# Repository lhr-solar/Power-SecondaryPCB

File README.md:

# Power-SecondaryPCB 
Author: Pratyush Patra and Jason Kacines

This board takes inputs from the DCDC converter and the Supplemental Battery and selects which source to output to the fuse box. DCDC is the power from the high voltage primary battery pack that gets stepped down to 12V through the DCDC converter. The supplemental battery pack is the low voltage 12V NiMH battery pack. When DCDC is on, the board will select DCDC, and when DCDC is off, the board will select the Supplemental Battery. The supplemental should only be selected during ignition and the fault state. The board selects the source using a 10V zener diode that will breakdown once DCDC is above 10V.

This board also interfaces with both the Supplemental Monitoring PCB and Ignition Switch:
- For the Supplemental Monitoring PCB, this board sends the voltage of the Supplemental Battery out from J1. 
- For the Ignition Switch, this board sends Supplemental Power to the Controls Board through J6, which is then routed back to this board through J7 when the Ignition Switch is changed from the off position. When this signal is sent to J7, it is routed to the gate of Q3 which turns on the NMOS and starts sending power to the fuse box.

## BOM
[**Interactive BOM (Must download and open in browser)**](bom/ibom.html)

[**Mouser Cart**](https://www.mouser.com/ProjectManager/ProjectDetail.aspx?AccessID=da938bf7b6)

## Connectors
| # | Name | Type | Ideal Voltage | Notes |
| - | - | - | - | - |
| J1  | SUPP PWR MON | 1x02_P3.00mm_Vertical Female | +12V | 9.9 mm tall |
| J2  | SUPP PWR 1 | 1x02_P7.49mm_Vertical Female |+12V | 14.76 mm tall |
| J3  | SUPP PWR 2 | 1x02_P7.49mm_Vertical Female | +12V | 14.76 mm tall |
| J4  | DCDC PWR | 1x02_P7.49mm_Vertical Female | +12V | 14.76 mm tall |
| J5  | FUSE OUT | 1x02_P7.49mm_Vertical Female | +12V | 14.76 mm tall |
| J6  | SUPP OUT | 1x02_P3.00mm_Vertical Female | +12V | 9.9 mm tall |
| J7  | LV ENABLE | 1x02_P3.00mm_Vertical Female | +12V | 9.9 mm tall |

## PCB

## Schematic

## Additional Notes
The tallest components are the Power MOSFETs(Q1A1, Q1A2, Q1A3, Q1A4) which are 18.5 mm tall and the connectors which are 14.76 mm tall.

## Current Board Concerns(8.26.2023)
- If the two Supplemental Batteries are at different voltage, don't want to charge batteries.
- If the two Supplemental Batteries are above 12V and DCDC is off, don't want to overvolt LV systems. 
        Can tolerate 12.8V.
- Should we use heat sinks for the MOSFET or switch to SMD in case we need to increase current draw in the future
- In future switch to this mosfet, https://www.mouser.com/datasheet/2/196/Infineon_IRFR5305_DataSheet_v01_01_EN-3166466.pdf

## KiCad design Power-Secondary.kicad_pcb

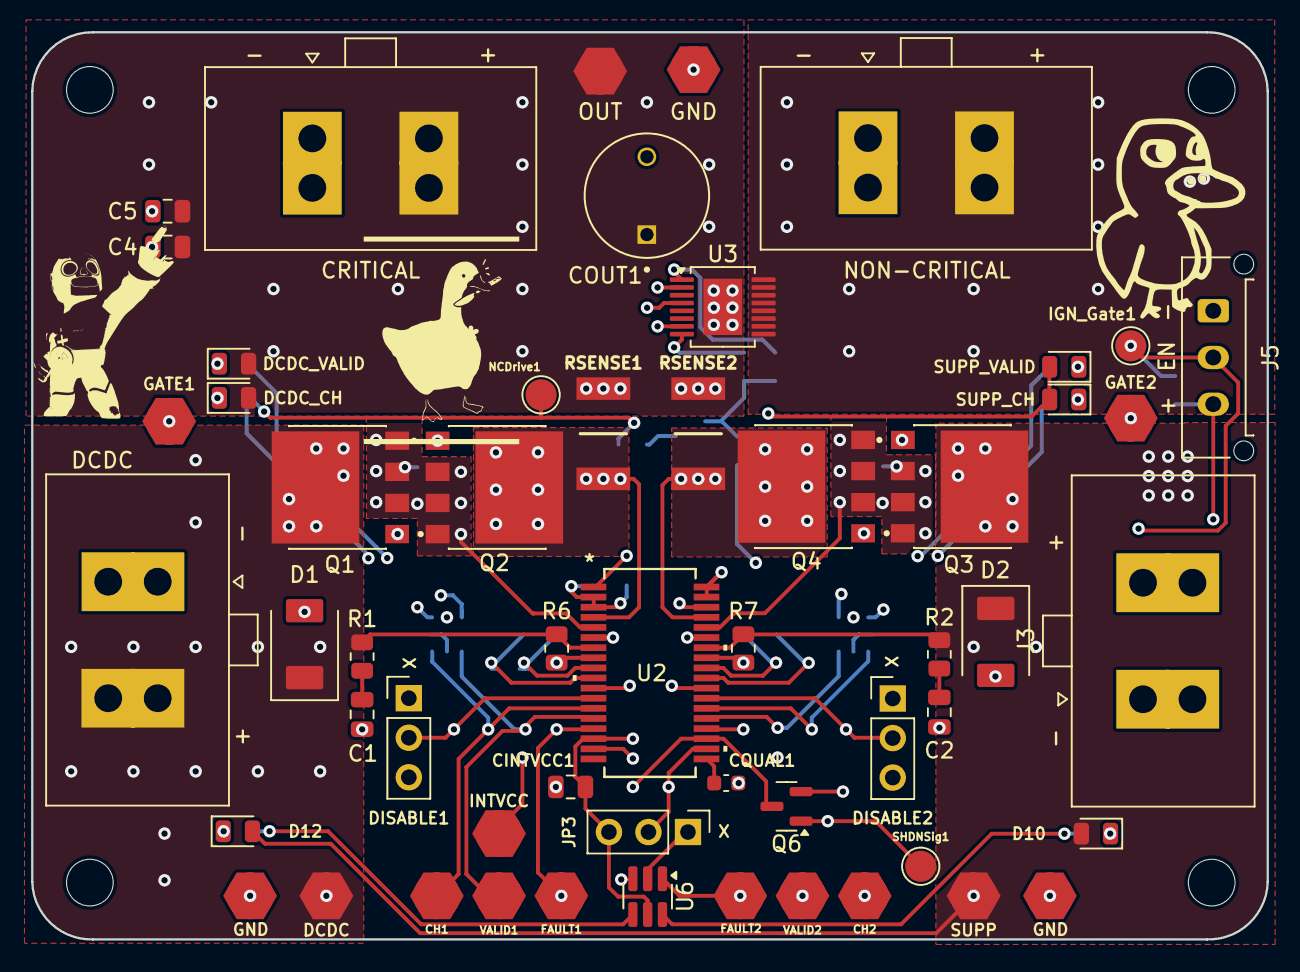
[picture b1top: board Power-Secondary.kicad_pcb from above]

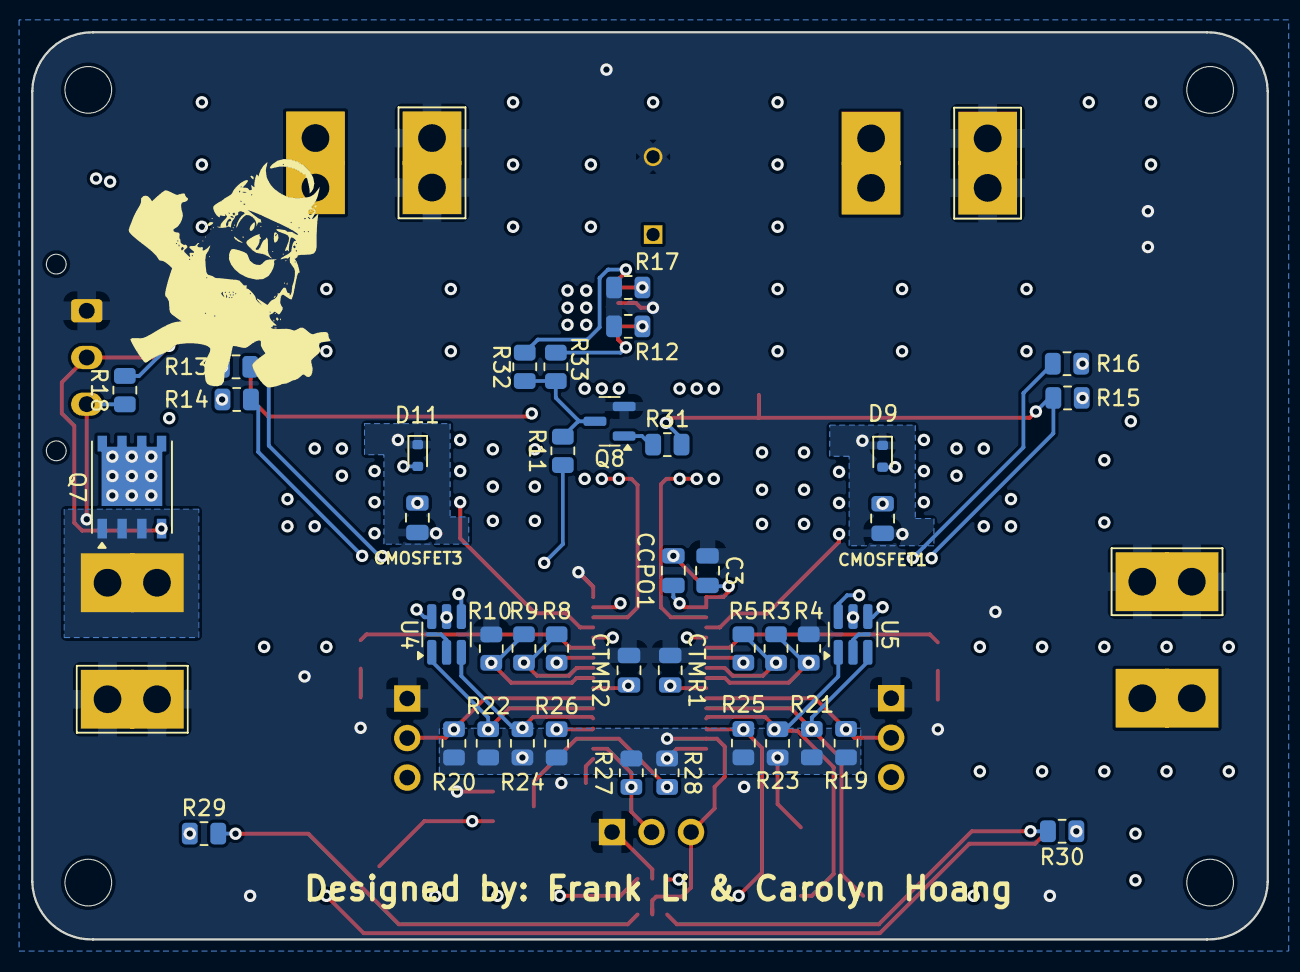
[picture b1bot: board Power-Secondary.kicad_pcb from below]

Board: 4 copper layers, 79.4 x 58.3 mm, 98 parts (41 on the bottom side), 54 nets.

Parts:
C1, C2, C4: 10u; C_0805_2012Metric
C3, C5: 0.1u; C_0805_2012Metric
CCPO1: 1u; C_0805_2012Metric
CH1, CH2: TestPoint; TestPoint_HEX_3mmID
CINTVCC1: 1u; C_0805_2012Metric
CMOSFET1, CMOSFET3: 10u; C_0805_2012Metric
COUT1: 1.2m; EEUFS1C122LB
CQUAL1: 500p; C_0603_1608Metric
CRITICAL: PowerConn; Molex_Sabre_43160-0102_1x02_P7.49mm_Vertical
CTMR1, CTMR2: 10u; C_0805_2012Metric
D1, D2: SMBJ15D-M3I; P26_DO-214AA_SMB
D9, D11: D_Zener; D_SOD-523
D10, D12: LED; LED_0805_2012Metric
DCDC: TestPoint; TestPoint_HEX_3mmID
DCDC#2: PowerConn; Molex_Sabre_43160-0102_1x02_P7.49mm_Vertical
DCDC_CH: LED; LED_0805_2012Metric
DCDC_VALID: LED; LED_0805_2012Metric
DISABLE1: DIS1 Jumper; PinHeader_1x03_P2.54mm_Vertical
DISABLE2: DIS2 Jumper; PinHeader_1x03_P2.54mm_Vertical
FAULT1, FAULT2: TestPoint; TestPoint_HEX_3mmID
GATE1, GATE2: TestPoint; TestPoint_HEX_3mmID
GND: TestPoint; TestPoint_HEX_3mmID
H1, H2, H3, H4: MountingHole; MountingHole_3mm
IGN_Gate1: TestPoint; TestPoint_Pad_D2.0mm
INTVCC: TestPoint; TestPoint_HEX_3mmID
J3: PowerConn; Molex_Sabre_43160-0102_1x02_P7.49mm_Vertical
J5: Conn_01x03; Molex_Micro-Fit_3.0_43650-0315_1x03_P3.00mm_Vertical
JP3: RETRY Jumper; PinHeader_1x03_P2.54mm_Vertical
NCDrive1: TestPoint; TestPoint_Pad_D2.0mm
NON-CRITICAL: PowerConn; Molex_Sabre_43160-0102_1x02_P7.49mm_Vertical
OUT: TestPoint; TestPoint_HEX_3mmID
Q1, Q2, Q3, Q4: SQJQ140E-T1_GE3; TO200P800X182-5N
Q6: NMOS; SOT-23
Q7: PMOS; PowerPAK_SO-8_Single
Q8: 2N7002; SOT-23
R1, R2: 1.2; R_0805_2012Metric
R3, R9: 5.1K; R_0805_2012Metric
R4, R10: 40K; R_0805_2012Metric
R5, R8: 3K; R_0805_2012Metric
R6, R7: 1M; R_0805_2012Metric
R11, R18: 100k; R_0805_2012Metric
R12: 1k; R_0805_2012Metric
R13, R14, R15, R16, R19, R20, R21, R22, R23, R24, R25, R26, R27, R28, R29, R30: 100K; R_0805_2012Metric
R17, R32, R33: 15k; R_0805_2012Metric
R31: 10k; R_0805_2012Metric
RSENSE1, RSENSE2: 1m; RESC6432X89N
SHDNSig1: TestPoint; TestPoint_Pad_D2.0mm
SUPP: TestPoint; TestPoint_HEX_3mmID
SUPP_CH: LED; LED_0805_2012Metric
SUPP_VALID: LED; LED_0805_2012Metric
U2: LTC4421CG-PBF; G_05-08-1640_ADI
U3: VND9016AJ; PowerSSO-16-1EP_3.9x4.9mm_P0.5mm_EP2.5x3.61mm
U4, U5, U6: 74LVC2G07GV,125; SC-74-6_1.55x2.9mm_P0.95mm
VALID1, VALID2: TestPoint; TestPoint_HEX_3mmID

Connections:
/GATE1: CMOSFET1.1, D9.1 (K), GATE1.1, Q1.1, Q2.1, U2.6 (GATE1)
/GATE2: CMOSFET3.1, D11.1 (K), GATE2.1, Q3.1, Q4.1, U2.31 (GATE2)
/INTVCC: CINTVCC1.1, INTVCC.1, JP3.3 (B), R11.1, R19.1, R20.1, R21.1, R22.1, R23.1, R24.1, R25.1, R26.1, R27.1, R28.1, U2.16 (CASIN), U2.17 (INTVCC), U4.5 (VCC), U5.5 (VCC), U6.5 (VCC)
/LTC4421/CH1: CH1.1, R21.2, U2.13 (*CH1), U5.3 (2A)
/LTC4421/CH2: CH2.1, R22.2, U2.24 (*CH2), U4.1 (1A)
/LTC4421/CPO: CCPO1.1, U2.1 (CPO)
/LTC4421/DISABLE1: DISABLE1.2 (C), R19.2, U2.12 (*DISABLE1)
/LTC4421/DISABLE2: DISABLE2.2 (C), R20.2, U2.25 (*DISABLE2)
/LTC4421/FAULT1: DISABLE1.3 (B), FAULT1.1, R25.2, U2.15 (*FAULT1), U6.3 (2A)
/LTC4421/FAULT2: DISABLE2.3 (B), FAULT2.1, R26.2, U2.22 (*FAULT2), U6.1 (1A)
/LTC4421/OV1: R3.2, R4.1, U2.10 (OV1)
/LTC4421/OV2: R9.2, R10.1, U2.27 (OV2)
/LTC4421/QUAL: CQUAL1.1, U2.19 (QUAL)
/LTC4421/RETRY: JP3.2 (C), R27.2, U2.20 (RETRY)
/LTC4421/SENSE1: Q2.5, RSENSE1.1, U2.4 (SENSE1)
/LTC4421/SENSE2: Q4.5, RSENSE2.1, U2.33 (SENSE2)
/LTC4421/TMR1: CTMR1.1, U2.11 (TMR1)
/LTC4421/TMR2: CTMR2.1, U2.26 (TMR2)
/LTC4421/UVF1: R5.1, R6.2, U2.8 (UVF1)
/LTC4421/UVF2: R7.2, R8.1, U2.29 (UVF2)
/LTC4421/UVR1: R3.1, R5.2, U2.9 (UVR1)
/LTC4421/UVR2: R8.2, R9.1, U2.28 (UVR2)
/LTC4421/VALID1: R23.2, U2.14 (*VALID1), U5.1 (1A), VALID1.1
/LTC4421/VALID2: R24.2, U2.23 (*VALID2), U4.3 (2A), VALID2.1
/Non-Crit Drive: NCDrive1.1, R15.2, R31.2, U5.4 (2Y)
/OUT: C3.1, C4.1, C5.1, CCPO1.2, COUT1.1, CRITICAL.2, DCDC_CH.2 (A), DCDC_VALID.2 (A), OUT.1, RSENSE1.2, RSENSE2.2, SUPP_CH.2 (A), SUPP_VALID.2 (A), U2.2 (CPOREF), U2.3 (OUT1), U2.34 (OUT2), U3.17 (VCC)
/SHDN: Q6.1 (D), R28.2, U2.21 (*SHDN)
/SHDN_sig: Q6.2 (G), R13.2, SHDNSig1.1, U4.4 (2Y)
/SOURCE1: CMOSFET1.2, D9.2 (A), Q1.2, Q1.3, Q1.4, Q2.2, Q2.3, Q2.4, U2.5 (SOURCE1)
/SOURCE2: CMOSFET3.2, D11.2 (A), Q3.2, Q3.3, Q3.4, Q4.2, Q4.3, Q4.4, U2.32 (SOURCE2)
/V1: D1.1 (K), DCDC.1, DCDC#2.2, Q1.5, R1.1, R6.1, U2.7 (V1)
/V2: D2.1 (K), D10.2 (A), D12.2 (A), Q3.5, Q7.1 (D), R2.1, R7.1, SUPP.1, U2.30 (V2)
GND: C1.2, C2.2, C3.2, C4.2, C5.2, CINTVCC1.2, COUT1.2, CQUAL1.2, CRITICAL.1, CTMR1.2, CTMR2.2, D1.2 (A), D2.2 (A), DCDC#2.1, DISABLE1.1 (A), DISABLE2.1 (A), GND.1, J3.1, J5.1, JP3.1 (A), NON-CRITICAL.1, Q6.3 (S), Q8.2 (S), R4.2, R10.2, R12.2, R17.1, U2.35 (GND), U2.36 (EXTVCC), U3.4 (GND), U4.2 (GND), U5.2 (GND), U6.2 (GND)
unnamed: C1.1, R1.2
unnamed: C2.1, R2.2
unnamed: R13.1, SUPP_VALID.1 (K)
unnamed: R14.1, SUPP_CH.1 (K)
unnamed: DCDC_CH.1 (K), R15.1
unnamed: DCDC_VALID.1 (K), R16.1
unnamed: D10.1 (K), R29.1
unnamed: D12.1 (K), R30.1
unnamed: J3.2, J5.3, Q7.3 (S), R18.1
unnamed: NON-CRITICAL.2, U3.9 (OUTPUT1), U3.10 (OUTPUT1), U3.11 (OUTPUT1), U3.12 (OUTPUT1), U3.13 (OUTPUT0), U3.14 (OUTPUT0), U3.15 (OUTPUT0), U3.16 (OUTPUT0)
unnamed: IGN_Gate1.1, J5.2, Q7.2 (G), R18.2
unnamed: Q8.3 (D), R11.2, R32.2, R33.2
unnamed: Q8.1 (G), R31.1
unnamed: R12.1, U3.7 (CS)
unnamed: R32.1, U3.1 (INPUT0)
unnamed: R33.1, U3.8 (INPUT1)
unnamed: R17.2, U3.2 (~FAULTRST)
unnamed: R14.2, U4.6 (1Y)
unnamed: R16.2, U5.6 (1Y)
unnamed: R29.2, U6.6 (1Y)
unnamed: R30.2, U6.4 (2Y)

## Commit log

2020-08-02 Separate the primary battery board to its own repo.
2020-08-31 Updated PBB to better match Hannah's standards
2020-09-01 Adds power planes to secondary power board
2020-09-01 Updates schematics to match secondary power board v1.1
2020-09-01 Adds gitignore file
2020-09-27 Adds 1st draft of PULL_REQUEST_TEMPLATE.md to test
2020-10-01 Updates QAC with two more bullet points
2020-10-03 Creates and deletes gerbers for release and finishes routing tracks
2020-10-03 Adds dimensions to PCB
2020-10-10 Add STEP model of board
2020-10-17 Secondary board v1.1 (#2)
    * Updated PBB to better match Hannah's standards
    * Adds power planes to secondary power board
    * Updates schematics to match secondary power board v1.1
    * Adds gitignore file
    * Creates and deletes gerbers for release and finishes routing tracks
    * Adds dimensions to PCB
2020-10-17 Adds pdf and png of documentation of schematic and pcb
2020-12-19 Combines disconnect and main supply for BPS into one connector
2021-01-11 Rearranges labels and adds gerbers
2021-01-11 Secondary Power Board CDR Edits (#3)
    * Combines disconnect and main supply for BPS into one connector
    * Rearranges labels and adds gerbers
2021-01-23 adds 3D models
2022-10-15 first
2022-12-05 secondary power pcb v2
    Changed schematic, removed unnecessary/old files
2023-01-14 version 3
2023-01-14 v3 update
2023-01-21 v3 revision
2023-01-21 added planes
2023-01-21 gerbers and fuse
2023-01-21 QUAC and readme
2023-01-28 added supp monitor connector
2023-01-28 gerbers
2023-01-28 removed excess
2023-01-28 updated gerbers and fixed clearence issues
2023-01-29 Added BOM
2023-02-06 Paj (#4)
    * first
    * secondary power pcb v2
    Changed schematic, removed unnecessary/old files
    * version 3
    * v3 update
    * v3 revision
2023-03-09 new diode board
2023-03-09 inverter
2023-03-10 New design made
2023-03-10 Fixed PMOS orientation, added testpoints
2023-03-10 Made gerber files. Added dimensions
2023-03-10 Made some traces wider
2023-05-22 Updated submodule
2023-05-22 Updated QAC
2023-05-22 Deleted extra QAC
2023-05-22 Updated BOM
2023-05-22 Added images of PCB schematic and layout
2023-05-22 Updated constraints
2023-05-29 Updated README with BOM
2023-05-29 Updated images
2023-05-29 Fixed README
2023-06-02 Updated Datasheets
2023-06-02 Added Excel BOM
2023-06-05 Fixed DRC and ERC errors in Kicad 7
2023-06-13 Updated 3D models
2023-06-13 Updated README and version history
2023-06-14 Fix BOM in README
2023-07-11 Replaced resistor divider with zener
2023-07-17 Corrected gate labels
2023-08-10 Updated layout with zener diode
2023-08-12 Updated schematic to interface with ignition switch
2023-08-20 Updated layout
2023-08-20 Updated pdfs
2023-08-22 Updated BOMs
2023-08-26 Fixed README format
2023-08-26 Rerouted traces
2023-08-26 Updated README notes
2023-08-29 Updated gerbers
2023-09-02 Fixed traces
2023-09-20 V4.2 (#7)
    * Updated submodule
    * Updated QAC
    * Deleted extra QAC
    * Updated BOM
    * Added images of PCB schematic and layout
    * Updated constraints
2023-09-21 V4.2 (#8)
    * Updated submodule
    * Updated QAC
    * Deleted extra QAC
    * Updated BOM
    * Added images of PCB schematic and layout
    * Updated constraints
2024-02-13 Added inverter
2024-03-29 bunch of stuff
2024-03-29 a bunch of code
2024-03-29 fixing stuff
2024-03-29 bunch of code
2024-03-29 attempt at Power Board software :)
2024-03-29 added fix to GPIO writes and some comments
2024-03-30 fixed moving avg filter
2024-04-01 Updated software
2024-04-01 Updated schematic
2024-04-01 Fixed zone identifier issue
2024-04-03 Designed PCB layout for new Power Board
2024-04-03 remove common submodule and added UTSVT-KiCadLibraries
2024-04-03 changed KiCad symbol and footprint libraries
2024-04-03 silkscreen changes
2024-04-06 PCB changes
2024-04-07 dual power board sch
2024-04-08 Schematic redesign
2024-04-12 sch changes
2024-04-12 layout changes
2024-04-12 fixes to power zones
2024-04-12 small change to trace
2024-04-13 silk screen changes
2024-04-13 ooga booga
2024-04-15 zone changes
2024-04-15 Fixed trace issue
2024-04-15 Fixed one wire
2024-06-03 new code
2024-06-30 Fixing issue
2024-09-22 LTC4421 Symbol creation
2024-09-23 early sch
2024-10-05 Improved organization of sch
2024-10-05 added circuitry for sch
2024-10-05 Added MOSFET to symbol library
2024-10-06 Finished sch
2024-10-11 footprint assignments
2024-10-12 changes to Power Board sch
2024-10-12 CAD models, symbols update, and footprints
2024-10-12 Pull up and Pull down configs for VALID, DISABLE, SHDN, RETRY
2024-10-18 small changes
2024-10-20 Library fixes and sch changes
2024-10-20 changes to sch
2024-10-26 assigned footprints
2024-10-26 Excel calculator
2024-10-26 Adjusted resistor divider values and specified more components in the BOM
2024-10-26 Completed BOM for the most part
2024-10-26 sch iteration 1 complete plssssssssss
2024-10-29 final footprint assignments
2024-11-02 initial layout
2024-11-02 added another current sense resistor
2024-11-02 fixed connector pinout
2024-11-02 change SHDN logic
2024-11-06 Readjustments to component placement v2.0
2024-11-06 A couple more readjustments esp to the visibility of silks
2024-11-07 Adjustments to the layout: low current on the back and in the middle and high current on the top
2024-11-08 More adjustments :O
2024-11-09 fixes to sch
2024-11-09 Placement and some routing
2024-11-10 Last few things to route and place: leds and the leftover testpoints
2024-11-10 Completed routing and placement
2024-11-12 Completed routing for v2.0 but it looks quite scuffed
2024-11-13 Minor adjustments in routing
2024-11-16 layout complete
2024-11-23 Layout fixes
2024-11-25 made all planes solid filled
2024-11-27 added supp mon connection
2024-11-29 constraint fixes
2025-02-21 Ltc4421 v1.0 (#12)
    * LTC4421 Symbol creation
    * early sch
    * early sch
    * changes
    * Improved organization of sch
    * added circuitry for sch
2025-04-09 fixes for IGN and non-crit
2025-04-12 SHDN, non-crit, and ignition sequence fixes
2025-06-13 bruh changes
2025-06-13 more bruh changes
2025-06-16 add high side switch schematic
2025-06-16 Non-crit layout
2025-06-16 addressing DRC errors
2025-06-16 removed changxu's face
2025-06-17 changed UV and OV resistor circuit
2025-06-17 added auto-retry functionality
2025-06-18 added testpoints for shdn sig and non-crit enable
2025-06-18 added fault LEDs
2025-06-18 made C3 do not populate
2025-06-28 resistors for FET gate and high side switch
